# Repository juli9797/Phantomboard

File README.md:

# Phantomboard
My attempt to build a 48V Phantom-Powersupply for audio equipment [UNTESTED]

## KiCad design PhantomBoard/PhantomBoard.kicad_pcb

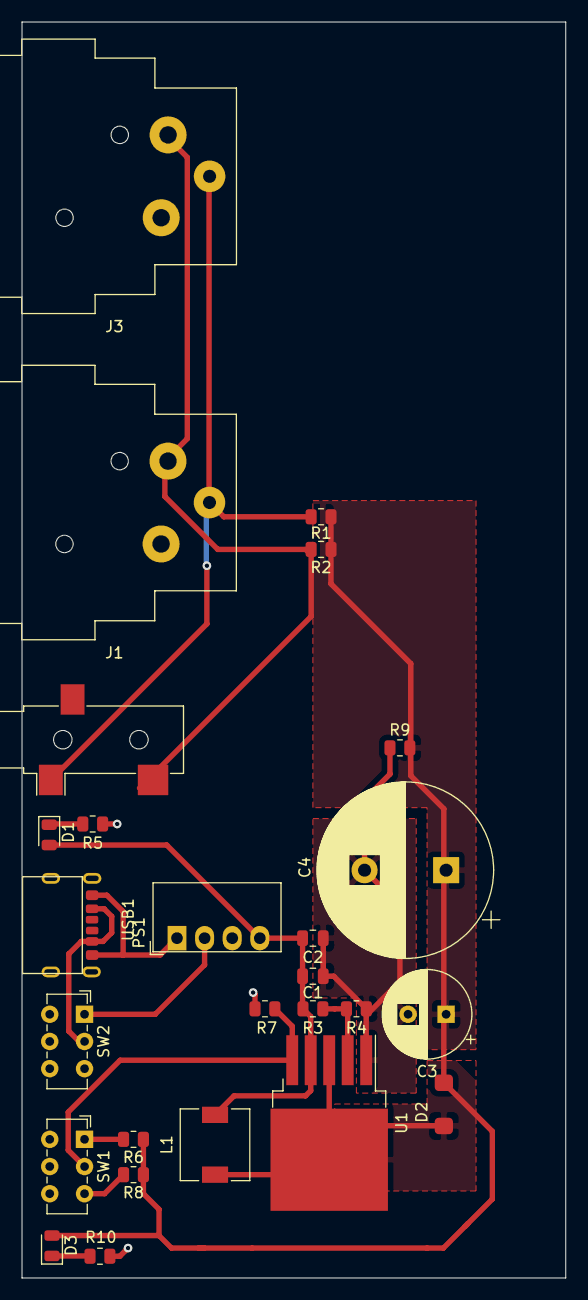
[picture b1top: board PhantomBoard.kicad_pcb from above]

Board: 2 copper layers, 50.0 x 115.5 mm, 26 parts (0 on the bottom side), 15 nets.

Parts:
C1: 47uF; C_0805_2012Metric
C2: 10uF; C_0805_2012Metric
C3: 10u; CP_Radial_D8.0mm_P3.50mm
C4: 220u; CP_Radial_D16.0mm_P7.50mm
D1, D3: LED; LED_0805_2012Metric
D2: DIODE; DO-214ac
J1, J3: XLR3; Jack_XLR_Neutrik_NC3FAAH-0_Horizontal
J2: AudioJack2; Jack_3.5mm_CUI_SJ-3523-SMT_Horizontal
L1: 33uH; L_6.3x6.3_H3
PS1: MEE1S0505SC; Converter_DCDC_Murata_MEE1SxxxxSC_THT
R1: 6R8; R_0805_2012Metric
R2: 6k8; R_0805_2012Metric
R3, R4: 0; R_0805_2012Metric
R5: 4k7; R_0805_2012Metric
R6: 39k; R_0805_2012Metric
R7, R9: 1k; R_0805_2012Metric
R8: 8k6; R_0805_2012Metric
R10: 47k; R_0805_2012Metric
SW1, SW2: SW_SPDT; SW_E-Switch_EG1271_DPDT
U1: XL6009; TO-263-5_TabPin3
USB1: USB_C_Power_Only; UJC-HP-3-SMT-TR

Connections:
5V: C1.1, C2.1, D1.2, L1.2, PS1.4, R3.1, U1.4
48V: C3.1, C4.1, D2.2, D3.2, R1.2, R2.1, R6.1, R8.1, R9.2
/Vsw: D2.1, L1.1, U1.3
GND: C1.2, C2.2, C3.2, C4.2, J1.1, J3.1, PS1.3, R4.2, R5.2, R7.1, R9.1, R10.2, U1.1
GNDD: PS1.1, USB1.1
unnamed: D1.1, R5.1
unnamed: D3.1, R10.1
unnamed: J1.2, J2.T, J3.2, R2.2
unnamed: J1.3, J2.S, J3.3, R1.1
unnamed: PS1.2, SW2.1
unnamed: R3.2, R4.1, U1.2
unnamed: R6.2, SW1.1
unnamed: R7.2, SW1.2, U1.5
unnamed: R8.2, SW1.3
unnamed: SW2.2, USB1.2

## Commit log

2020-11-26 init
2020-11-26 added gitignore
2020-11-26 schematic fixed
